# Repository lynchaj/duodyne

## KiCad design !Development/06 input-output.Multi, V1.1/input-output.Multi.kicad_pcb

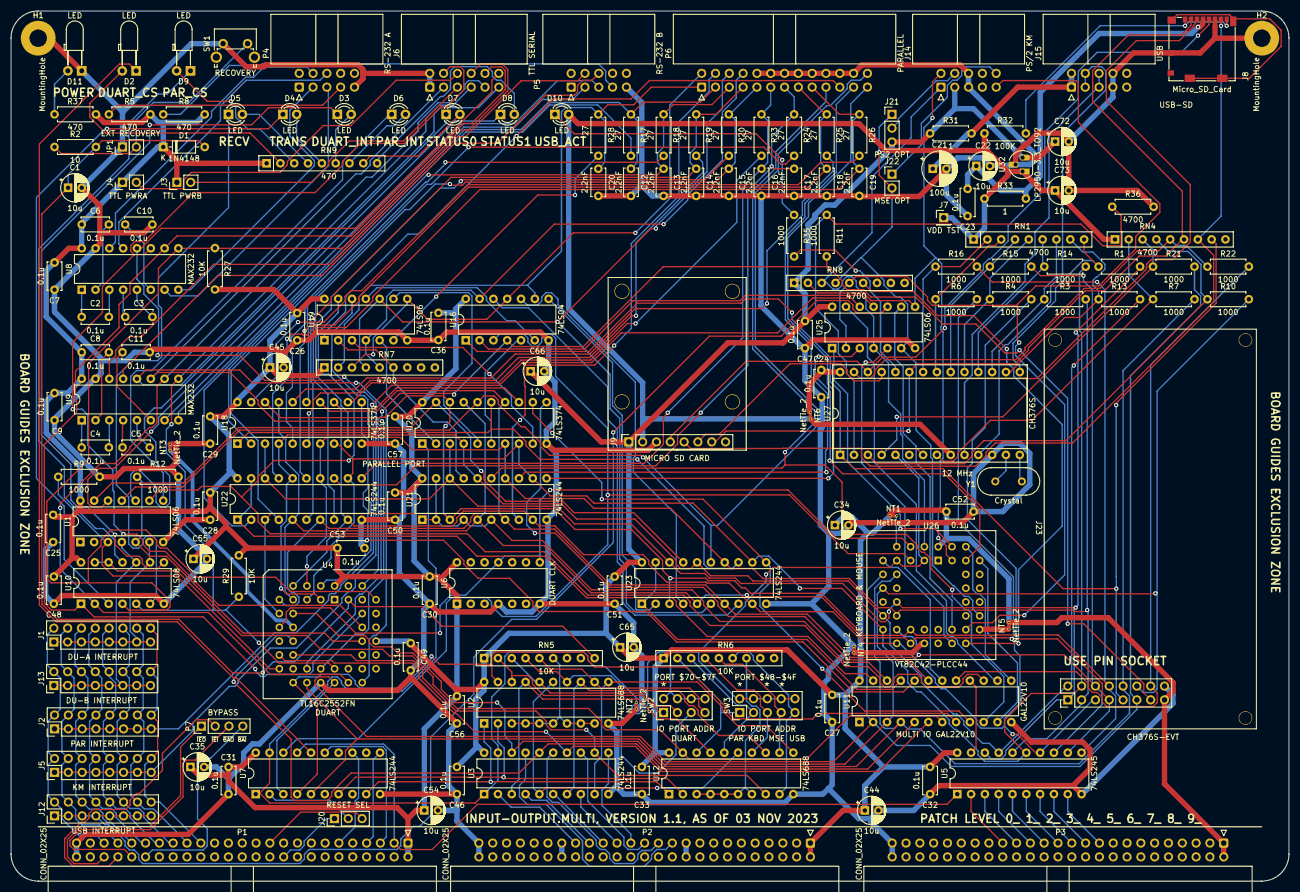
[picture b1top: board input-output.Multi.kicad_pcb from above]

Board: 2 copper layers, 235.0 x 160.0 mm, 167 parts (0 on the bottom side), 230 nets.

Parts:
C1, C22, C34, C35, C44, C45, C54, C55, C65, C66, C72, C73: 10u; CP_Radial_D5.0mm_P2.50mm
C2, C3, C4, C5, C6, C7, C8, C9, C10, C11, C23, C24, C25, C26, C27, C28, C29, C30, C31, C32, C33, C36, C46, C47, C48, C49, C50, C51, C52, C53, C56, C57: 0.1u; C_Disc_D5.0mm_W2.5mm_P5.00mm
C12, C13, C14, C15, C16, C17, C18, C19, C20: 2.2nF; C_Disc_D5.0mm_W2.5mm_P5.00mm
C21: 100u; CP_Radial_D6.3mm_P2.50mm
D1: 1N4148; D_DO-35_SOD27_P7.62mm_Horizontal
D2, D9, D11: LED; LED_D3.0mm_Horizontal_O3.81mm_Z2.0mm
D3, D4, D5, D6, D7, D8, D10: LED; LED_D3.0mm
H1, H2: MountingHole; MountingHole_3.2mm_M3_Pad
J1: DU-A INTERRUPT; PinHeader_2x08_P2.54mm_Vertical
J2: PAR INTERRUPT; PinHeader_2x08_P2.54mm_Vertical
J3: TTL PWRB; PinHeader_1x02_P2.54mm_Vertical
J4: TTL PWRA; PinHeader_1x02_P2.54mm_Vertical
J5: KM INTERRUPT; PinHeader_2x08_P2.54mm_Vertical
J6: TTL SERIAL; IDC-Header_2x06_P2.54mm_Horizontal
J7: VDD TST; PinHeader_1x01_P2.54mm_Vertical
J8: Micro_SD_Card; microSD_HC_Molex_104031-0811
J9: MICRO SD CARD; Adafruit MicroSD Module
J12: USB INTERRUPT; PinHeader_2x08_P2.54mm_Vertical
J13: DU-B INTERRUPT; PinHeader_2x08_P2.54mm_Vertical
J14: PS/2 KM; IDC-Header_2x05_P2.54mm_Horizontal
J15: USB; IDC-Header_2x05_P2.54mm_Horizontal
J20: RESET SEL; PinHeader_1x03_P2.54mm_Vertical
J21: PS2 OPT; PinHeader_1x03_P2.54mm_Vertical
J22: MSE OPT; PinHeader_1x02_P2.54mm_Vertical
J23: CH376S-EVT
JP1: EXT RECOVERY; PinHeader_1x02_P2.54mm_Vertical
NT1, NT2, NT3, NT4, NT5, NT6: NetTie_2; NetTie-2_THT_Pad0.3mm
P1, P2, P3: CONN_02X25; IDC-Header_2x25_P2.54mm_Horizontal
P4: RS-232 A; IDC-Header_2x05_P2.54mm_Horizontal
P5: RS-232 B; IDC-Header_2x05_P2.54mm_Horizontal
P6: PARALLEL; IDC-Header_2x13_P2.54mm_Horizontal
P7: BYPASS; PinHeader_1x04_P2.54mm_Vertical
R1, R3, R4, R6, R7, R9, R10, R11, R12, R13, R14, R15, R16, R21, R22, R35: 1000; R_Axial_DIN0207_L6.3mm_D2.5mm_P7.62mm_Horizontal
R2: 10; R_Axial_DIN0207_L6.3mm_D2.5mm_P7.62mm_Horizontal
R5, R8, R37: 470; R_Axial_DIN0207_L6.3mm_D2.5mm_P7.62mm_Horizontal
R17, R18, R19, R20, R23, R24, R25, R26, R28: 27; R_Axial_DIN0207_L6.3mm_D2.5mm_P7.62mm_Horizontal
R27, R29: 10K; R_Axial_DIN0207_L6.3mm_D2.5mm_P7.62mm_Horizontal
R31, R33: 1; R_Axial_DIN0207_L6.3mm_D2.5mm_P7.62mm_Horizontal
R32: 100K; R_Axial_DIN0207_L6.3mm_D2.5mm_P7.62mm_Horizontal
R36: 4700; R_Axial_DIN0207_L6.3mm_D2.5mm_P7.62mm_Horizontal
RN1, RN4, RN7, RN8: 4700; R_Array_SIP9
RN5, RN6: 10K; R_Array_SIP9
RN9: 470; R_Array_SIP9
SW1: RECOVERY; SW_Tactile_SPST_Angled_PTS645Vx58-2LFS
SW2: IO PORT ADDR; PinHeader_2x04_P2.54mm_Vertical
SW3: IO PORT ADDR; PinHeader_2x05_P2.54mm_Vertical
U1, U19, U25: 74LS06; DIP-14_W7.62mm
U2, U12: 74LS688; DIP-20_W7.62mm
U3, U7, U21, U22, U23: 74LS244; DIP-20_W7.62mm
U4: TL16C2552FN; PLCC-44_THT-Socket
U5: 74LS245; DIP-20_W7.62mm
U6: DUART CLK; DIP-14_W7.62mm
U8, U9: MAX232; DIP-16_W7.62mm
U10: 74LS08; DIP-14_W7.62mm
U11: GAL22V10; DIP-24_W7.62mm
U16: 74LS04; DIP-14_W7.62mm
U18, U20: 74LS374; DIP-20_W7.62mm
U26: VT82C42-PLCC44; PLCC-44_THT-Socket
U27: CH376S; DIP-28_W15.24mm_Socket
U32: LP2950-3.3_TO92; TO-92_HandSolder
Y1: Crystal; Crystal_HC49-4H_Vertical

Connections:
470A: D2.2 (A), RN9.2 (R1)
470B: D9.2 (A), RN9.3 (R2)
470C: D5.2 (A), RN9.4 (R3)
470D: D4.2 (A), RN9.5 (R4)
470E: D3.2 (A), RN9.6 (R5)
470F: D6.2 (A), RN9.7 (R6)
470G: D7.2 (A), RN9.8 (R7)
470H: D8.2 (A), RN9.9 (R8)
+12V: P2.19, P2.20
-12V: P2.37, P2.38
/DUART/GND_UART: NT3.1, U4.12 (GND)
/DUART/INTA: R12.1, U1.5, U4.34 (INTA)
/DUART/INTB: R9.1, U1.3, U4.17 (INTB)
/DUART/RXA: P4.3, U8.8 (R2IN)
/DUART/RXB: P5.3, U9.8 (R2IN)
/DUART/TTL_RXA: J6.8, R27.1, U4.39 (RXA), U8.9 (R2OUT), U10.4
/DUART/TTL_RXB: J6.7, R29.1, U4.25 (RXB), U9.9 (R2OUT), U10.5
/DUART/TTL_TXA: J6.10, U4.38 (TXA), U8.10 (T2IN), U10.1
/DUART/TTL_TXB: J6.9, U4.26 (TXB), U9.10 (T2IN), U10.2
/DUART/TXA: P4.5, U8.7 (T2OUT)
/DUART/TXB: P5.5, U9.7 (T2OUT)
/DUART/~CTSA: P4.6, U8.13 (R1IN)
/DUART/~CTSB: P5.6, U9.13 (R1IN)
/DUART/~DTRA: P4.7, R5.1
/DUART/~DTRB: P5.7, R8.1
/DUART/~INTA: J1.1, J1.3, J1.5, J1.7, J1.9, J1.11, J1.13, J1.15, U1.6, U10.9
/DUART/~INTB: J13.1, J13.3, J13.5, J13.7, J13.9, J13.11, J13.13, J13.15, U1.4, U10.10
/DUART/~RTSA: P4.4, U8.14 (T1OUT)
/DUART/~RTSB: P5.4, U9.14 (T1OUT)
/DUART/~TTL_CTSA: J6.12, U4.40 (~CTSA), U8.12 (R1OUT)
/DUART/~TTL_CTSB: J6.11, U4.28 (~CTSB), U9.12 (R1OUT)
/DUART/~TTL_RIA: C1.1, D1.2 (A), R2.2, RN5.9 (R8), U4.43 (~RIA)
/DUART/~TTL_RTSA: J6.4, U4.36 (~RTSA), U8.11 (T1IN)
/DUART/~TTL_RTSB: J6.3, U4.23 (~RTSB), U9.11 (T1IN)
/USB-SD/RST: R11.1, R36.1, U27.2 (RSTI)
/USB-SD/SDCK: J8.5 (CLK), J9.4, U27.26 (SD_CK)
/USB-SD/SDCS: J8.2 (DAT3/CD), J9.7, RN4.6 (R5), U27.23 (SD_CS)
/USB-SD/SDDI: J8.3 (CMD), J9.6, U27.25 (SD_DO)
/USB-SD/SDDO: J8.7 (DAT0), J9.5, RN4.7 (R6), U27.7 (SD_DI)
/USB-SD/UD+: J15.5, J15.6, U27.10 (UD+)
/USB-SD/UD-: J15.3, J15.4, U27.11 (UD-)
/USB-SD/VBUS: C21.1, J15.1, J15.2, R31.2
/USB-SD/VDD2: C24.1, NT6.1, U27.28 (VCC)
/USB-SD/VDD3: C22.1, C23.1, J8.4 (VDD), R33.2
/USB-SD/~INT-USB: J23.9, RN4.8 (R7), U16.1, U27.1 (~INT)
/kbdmse/KBDCLK: J14.1, RN8.3 (R2), U25.4, U26.2 (T0)
/kbdmse/KBDDAT: J14.9, RN8.5 (R4), U25.2, U26.30 (P10)
/kbdmse/MSECLK: J14.2, RN8.2 (R1), U25.8, U26.43 (T1)
/kbdmse/MSEDAT: J21.1, J22.2, RN8.4 (R3), U25.6, U26.31 (P11)
/kbdmse/PROG: RN8.6 (R5), U26.28 (PROG)
/kbdmse/~INT_KM: J5.1, J5.3, J5.5, J5.7, J5.9, J5.11, J5.13, J5.15, U25.12
/parallel/BUSY: RN7.6 (R5), U19.2, U21.17 (I3b)
/parallel/ERROR: P6.4, U21.8 (I3a)
/parallel/P-RESET: P6.6, RN7.4 (R3), U19.10, U23.6 (I2a)
/parallel/PAPEROUT: P6.23, U21.13 (I1b)
/parallel/PD0: C12.1, P6.3, R17.1, U22.2 (I0a)
/parallel/PD1: C13.1, P6.5, R18.1, U22.4 (I1a)
/parallel/PD2: C14.1, P6.7, R19.1, U22.6 (I2a)
/parallel/PD3: C15.1, P6.9, R20.1, U22.8 (I3a)
/parallel/PD4: C16.1, P6.11, R23.1, U22.11 (I0b)
/parallel/PD5: C17.1, P6.13, R24.1, U22.13 (I1b)
/parallel/PD6: C18.1, P6.15, R25.1, U22.15 (I2b)
/parallel/PD7: C19.1, P6.17, R26.1, U22.17 (I3b)
/parallel/SELECT: P6.25, U21.11 (I0b)
/parallel/STATUS0: P6.26, U1.11, U20.16 (O6), U23.15 (I2b)
/parallel/STATUS1: U1.13, U20.19 (O7), U23.17 (I3b)
/parallel/~BUSY: P6.21, U19.1
/parallel/~INT_PAR: J2.1, J2.3, J2.5, J2.7, J2.9, J2.11, J2.13, J2.15, U19.12
/parallel/~LINEFEED: P6.2, RN7.3 (R2), U16.11, U19.8
/parallel/~PDENBL: U18.1 (OE), U20.15 (O5), U23.13 (I1b)
/parallel/~SEL: P6.8, RN7.5 (R4), U16.13, U19.4
/parallel/~STROBE: C20.1, P6.1, R28.1, RN7.2 (R1), U16.9
A0: P2.35, U3.2 (I0a)
A1: P2.33, U3.4 (I1a)
A2: P2.31, U3.6 (I2a)
A3: P2.29, U3.8 (I3a)
A4: P2.27, U3.11 (I0b)
A5: P2.25, U3.13 (I1b)
A6: P2.23, U3.15 (I2b)
A7: P2.21, U3.17 (I3b)
ACK: P6.19, U11.10 (I9), U21.15 (I2b)
CLK_DUART: U4.11 (XTAL1), U6.8, U6.11, U26.4 (X2)
D0: P3.33, U5.2 (A0)
D1: P3.31, U5.3 (A1)
D2: P3.29, U5.4 (A2)
D3: P3.27, U5.5 (A3)
D4: P3.25, U5.6 (A4)
D5: P3.23, U5.7 (A5)
D6: P3.21, U5.8 (A6)
D7: P3.19, U5.9 (A7)
GND: C1.2, C7.2, C9.2, C10.2, C11.2, C12.2, C13.2, C14.2, C15.2, C16.2, C17.2, C18.2, C19.2, C20.2, C21.2, C22.2, C23.2, C24.2, C25.2, C26.2, C27.2, C28.2, C29.2, C30.2, C31.2, C32.2, C33.2, C34.2, C35.2, C36.2, C44.2, C45.2, C46.2, C47.2, C48.2, C49.2, C50.2, C51.2, C52.2, C53.2, C54.2, C55.2, C56.2, C57.2, C65.2, C66.2, C72.2, C73.2, D11.1 (K), H1.1, H2.1, J6.1, J6.2, J8.6 (VSS), J8.9 (SHIELD), J9.3, J14.5, J14.6, J15.7, J15.8, J23.16, JP1.1 (A), NT2.1, NT3.2, NT4.1, P1.49, P1.50, P2.49, P2.50, P3.49, P3.50, P4.9, P5.9, P6.10, P6.12, P6.14, P6.16, P6.18, P6.20, P6.22, P6.24, R9.2, R12.2, R36.2, SW1.1, U1.7 (GND), U2.10 (GND), U3.10 (GND), U4.22 (GND), U5.10 (GND), U6.4, U6.7, U7.10 (GND), U8.15 (GND), U9.15 (GND), U10.7 (GND), U11.12 (GND), U12.10 (GND), U16.7 (GND), U18.10 (GND), U19.7 (GND), U20.10 (GND), U21.10 (GND), U22.10 (GND), U23.10 (GND), U25.7 (GND), U27.12 (GND), U32.2 (GND)
INT_KM: U11.14 (O9), U25.13
INT_PAR: U1.9, U11.15 (O8), U19.13
unnamed: C2.1, U8.1 (C1+)
unnamed: C2.2, U8.3 (C1-)
unnamed: C3.1, U8.4 (C2+)
unnamed: C3.2, U8.5 (C2-)
unnamed: C4.1, U9.1 (C1+)
unnamed: C4.2, U9.3 (C1-)
unnamed: C5.1, U9.4 (C2+)
unnamed: C5.2, U9.5 (C2-)
unnamed: C6.2, U8.2 (VS+)
unnamed: C8.2, U9.2 (VS+)
unnamed: C10.1, U8.6 (VS-)
unnamed: C11.1, U9.6 (VS-)
unnamed: D2.1 (K), U7.16 (O1a)
unnamed: D3.1 (K), U10.8
unnamed: D4.1 (K), U10.3
unnamed: D5.1 (K), U10.6
unnamed: D6.1 (K), U1.8
unnamed: D7.1 (K), U1.10
unnamed: D8.1 (K), U1.12
unnamed: D9.1 (K), U10.11
unnamed: D10.1 (K), R35.1
unnamed: D11.2 (A), R37.1
unnamed: J3.2, J6.5
unnamed: J4.2, J6.6
unnamed: J8.1 (DAT2), J8.8 (DAT1), R32.2
unnamed: J12.1, J12.3, J12.5, J12.7, J12.9, J12.11, J12.13, J12.15, U25.10
unnamed: J14.4, J21.2
unnamed: J14.10, J22.1
unnamed: J20.2, U7.2 (I0a)
unnamed: JP1.2 (B), R2.1, SW1.2
unnamed: R1.1, RN1.9 (R8), U27.15 (D0)
unnamed: R3.1, RN1.7 (R6), U27.17 (D2)
unnamed: R4.1, RN1.5 (R4), U27.19 (D4)
unnamed: R6.1, RN1.3 (R2), U27.21 (D6)
unnamed: R7.1, RN4.2 (R1), U27.8 (A0)
unnamed: R10.1, RN4.4 (R3), U27.3 (~WR)
unnamed: R13.1, RN1.8 (R7), U27.16 (D1)
unnamed: R14.1, RN1.6 (R5), U27.18 (D3)
unnamed: R15.1, RN1.4 (R3), U27.20 (D5)
unnamed: R16.1, RN1.2 (R1), U27.22 (D7)
unnamed: R17.2, U18.2 (O0)
unnamed: R18.2, U18.5 (O1)
unnamed: R19.2, U18.6 (O2)
unnamed: R20.2, U18.9 (O3)
unnamed: R21.1, RN4.3 (R2), U27.4 (~RD)
unnamed: R22.1, RN4.5 (R4), U27.27 (~PCS)
unnamed: R23.2, U18.12 (O4)
unnamed: R24.2, U18.15 (O5)
unnamed: R25.2, U18.16 (O6)
unnamed: R26.2, U18.19 (O7)
unnamed: R28.2, U19.6
unnamed: R35.2, U27.24 (~ACT)
unnamed: RN5.2 (R1), SW2.1, U2.18 (R7)
unnamed: RN5.3 (R2), SW2.3, U2.16 (R6)
unnamed: RN5.4 (R3), SW2.5, U2.14 (R5)
unnamed: RN5.5 (R4), SW2.7, U2.12 (R4)
unnamed: RN5.6 (R5), U2.3 (R0), U2.4 (P1), U2.5 (R1), U2.6 (P2), U2.7 (R2), U2.8 (P3), U2.9 (R3)
unnamed: RN6.2 (R1), SW3.1, U12.18 (R7)
unnamed: RN6.3 (R2), SW3.3, U12.16 (R6)
unnamed: RN6.4 (R3), SW3.5, U12.14 (R5)
unnamed: RN6.5 (R4), SW3.7, U12.12 (R4)
unnamed: RN6.6 (R5), SW3.9, U12.9 (R3)
unnamed: RN6.7 (R6), U12.3 (R0), U12.4 (P1), U12.5 (R1), U12.6 (P2), U12.7 (R2)
unnamed: U16.2, U25.11
unnamed: U16.5, U20.6 (O2)
unnamed: U16.6, U19.11
unnamed: U16.8, U23.2 (I0a)
unnamed: U16.10, U23.4 (I1a)
unnamed: U16.12, U23.8 (I3a)
unnamed: U19.3, U20.9 (O3)
unnamed: U19.5, U20.2 (O0)
unnamed: U19.9, U20.5 (O1)
unnamed: U25.1, U26.42 (P27/DAK)
unnamed: U25.3, U26.41 (P26/DRQ)
unnamed: U25.5, U26.26 (P22)
unnamed: U25.9, U26.27 (P23)
unnamed: U27.13 (XI), Y1.1
unnamed: U27.14 (XO), Y1.2
ONE: NT1.2, U26.6 (SS)
P24-OB: U11.11 (I10), U26.39 (P24/OB)
P25-BF: U11.13 (I11), U26.40 (P25/BF)
PARINT: U11.9 (I8), U20.12 (O4), U23.11 (I0b)
VCC: C6.1, C7.1, C8.1, C9.1, C25.1, C26.1, C27.1, C28.1, C29.1, C30.1, C31.1, C32.1, C33.1, C34.1, C35.1, C36.1, C44.1, C45.1, C46.1, C47.1, C48.1, C49.1, C50.1, C51.1, C52.1, C53.1, C54.1, C55.1, C56.1, C57.1, C65.1, C66.1, C72.1, D1.1 (K), J3.1, J4.1, J9.1, J14.3, J21.3, J23.15, NT1.1, NT5.2, P1.1, P1.2, P2.1, P2.2, P3.1, P3.2, R5.2, R8.2, R27.2, R29.2, R31.1, R37.2, RN5.1 (common), RN6.1 (common), RN7.1 (common), RN8.1 (common), RN9.1 (common), U1.14 (VCC), U2.20 (VCC), U3.20 (VCC), U4.33 (VCC), U4.44 (VCC), U5.20 (VCC), U6.1, U6.14, U7.20 (VCC), U8.16 (VCC), U9.16 (VCC), U10.14 (VCC), U11.24 (VCC), U12.20 (VCC), U16.14 (VCC), U18.20 (VCC), U19.14 (VCC), U20.20 (VCC), U21.20 (VCC), U22.20 (VCC), U23.20 (VCC), U25.14 (VCC), U26.44 (VCC), U32.3 (VI)
VDD: NT5.1, U26.29 (VDD)
VDD1: C73.1, D10.2 (A), J7.1, J9.2, NT6.2, R32.1, R33.1, RN1.1 (common), RN4.1 (common), U27.9 (V3), U32.1 (VO)
VSS: NT4.2, U26.22 (VSS)
ZERO: NT2.2, SW2.2, SW2.4, SW2.6, SW2.8, SW3.2, SW3.4, SW3.6, SW3.8, SW3.10, U3.1 (OEa), U3.19 (OEb), U7.1 (OEa), U7.19 (OEb), U20.1 (OE), U26.3 (X1), U26.8 (EA), U27.5 (TXD)
bA0: J23.10, R7.2, U3.18 (O0a), U4.10 (A0), U11.4 (I3), U26.10 (A0)
bA1: U3.16 (O1a), U4.14 (A1), U11.5 (I4)
bA2: U3.14 (O2a), U4.15 (A2), U11.6 (I5)
bA3: U3.12 (O3a), U4.16 (CHSEL), U12.8 (P3)
bA4: U2.11 (P4), U3.9 (O0b), U12.11 (P4)
bA5: U2.13 (P5), U3.7 (O1b), U12.13 (P5)
bA6: U2.15 (P6), U3.5 (O2b), U12.15 (P6)
bA7: U2.17 (P7), U3.3 (O3b), U12.17 (P7)
bD0: J23.1, R1.2, U4.2 (D0), U5.18 (B0), U18.3 (D0), U20.3 (D0), U21.18 (O0a), U22.18 (O0a), U23.18 (O0a), U26.14 (D0)
bD1: J23.2, R13.2, U4.3 (D1), U5.17 (B1), U18.4 (D1), U20.4 (D1), U21.16 (O1a), U22.16 (O1a), U23.16 (O1a), U26.15 (D1)
bD2: J23.3, R3.2, U4.4 (D2), U5.16 (B2), U18.7 (D2), U20.7 (D2), U21.14 (O2a), U22.14 (O2a), U23.14 (O2a), U26.16 (D2)
bD3: J23.4, R14.2, U4.5 (D3), U5.15 (B3), U18.8 (D3), U20.8 (D3), U21.12 (O3a), U22.12 (O3a), U23.12 (O3a), U26.17 (D3)
bD4: J23.5, R4.2, U4.6 (D4), U5.14 (B4), U18.13 (D4), U20.13 (D4), U21.9 (O0b), U22.9 (O0b), U23.9 (O0b), U26.18 (D4)
bD5: J23.6, R15.2, U4.7 (D5), U5.13 (B5), U18.14 (D5), U20.14 (D5), U21.7 (O1b), U22.7 (O1b), U23.7 (O1b), U26.19 (D5)
bD6: J23.7, R6.2, U4.8 (D6), U5.12 (B6), U18.17 (D6), U20.17 (D6), U21.5 (O2b), U22.5 (O2b), U23.5 (O2b), U26.20 (D6)
bD7: J23.8, R16.2, U4.9 (D7), U5.11 (B7), U18.18 (D7), U20.18 (D7), U21.3 (O3b), U22.3 (O3b), U23.3 (O3b), U26.21 (D7)
bRESET: J23.13, R11.2, U4.21 (RESET), U16.4
~BAI: P1.40, P7.4
~BAO: P1.42, P7.3
~BUS_EN: U5.19 (CE), U11.16 (O7)
~CS_DUART: U2.19 (P=R), U4.18 (~CS), U7.4 (I1a), U11.8 (I7)
~CS_KM: U11.18 (O5), U26.7 (CS)
~CS_PAR: U10.12, U10.13, U11.7 (I6), U12.19 (P=R)
~CS_US: J23.14, R22.2, U11.17 (O6)
~EIRQ0: J1.2, J2.2, J5.2, J12.2, J13.2, P1.45
~EIRQ1: J1.4, J2.4, J5.4, J12.4, J13.4, P1.43
~EIRQ2: J1.6, J2.6, J5.6, J12.6, J13.6, P1.41
~EIRQ3: J1.8, J2.8, J5.8, J12.8, J13.8, P1.39
~EIRQ4: J1.10, J2.10, J5.10, J12.10, J13.10, P1.37
~EIRQ5: J1.12, J2.12, J5.12, J12.12, J13.12, P1.35
~EIRQ6: J1.14, J2.14, J5.14, J12.14, J13.14, P1.33
~EIRQ7: J1.16, J2.16, J5.16, J12.16, J13.16, P1.31
~IEI: P1.44, P7.2
~IEO: P1.46, P7.1
~IORQ: P1.7, U7.11 (I0b)
~M1: P1.11, U7.13 (I1b)
~PARIN0: U11.23 (O0), U22.1 (OEa), U22.19 (OEb)
~PARIN1: U11.22 (O1), U21.1 (OEa), U21.2 (I0a), U21.4 (I1a), U21.6 (I2a), U21.19 (OEb)
~PARIN2: U11.21 (O2), U23.1 (OEa), U23.19 (OEb)
~PAROUT0: U11.20 (O3), U18.11 (Cp)
~PAROUT2: U11.19 (O4), U20.11 (Cp)
~RD: P1.3, U5.1 (A->B), U7.17 (I3b)
~RES_IN: J20.1, P1.20
~RES_OUT: J20.3, P1.21
~WR: P1.5, U7.15 (I2b)
~bIORQ: U2.1 (G), U7.9 (O0b), U12.1 (G)
~bM1: U2.2 (P0), U7.7 (O1b), U12.2 (P0)
~bRD: J23.11, R21.2, U4.24 (~IOR), U7.3 (O3b), U11.2 (I1), U26.9 (RD)
~bRESET: U7.18 (O0a), U16.3, U26.5 (RESET)
~bWR: J23.12, R10.2, U4.20 (~IOW), U7.5 (O2b), U11.3 (I2), U26.11 (WR)

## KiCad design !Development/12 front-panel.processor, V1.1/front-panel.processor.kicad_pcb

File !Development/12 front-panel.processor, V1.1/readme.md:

The front-panel board connects to the Z80 processor to allow local access to configuration status input and display.  Also supports TTL serial to USB connection, an SSD1306 OLED display, and an I2C to SD card.  Several Z80 processor parameters can be set along with a reset button.

The I2C to SD card uses an ATtiny microcontroller which requires programming to work.  It is modeled after the I2C to SD card project at Technoblogy (http://www.technoblogy.com/show?3XEP)

Firmware for the card can be built and programed from the Arduino project located in the ATTINY_SD_FIRMWARE folder in this repo

You can program your ATtiny using the Arduino IDE for Linux 1.8.13 available here: https://www.arduino.cc/en/software/OldSoftwareReleases

with the megaTinyCore available here: https://wolles-elektronikkiste.de/en/using-megatinycore#usb2ttl_adaper_as_updi

I used a 3.3V TTL serial to USB cable direct to the UPDI connector on the front-panel and it worked fine. Following the instructions, I was able to successfully program the ATtiny1614 in-circuit. Alternatively, you can use pymcuprog on Linux.  Just follow the instructions here:https://pypi.org/project/pymcuprog/

For example, I was able to "ping" the ATtiny1614 and get a verbose status using: pymcuprog ping -d attiny1614 -t uart -u /dev/ttyUSB0 -v debug

Once programmed the ATTINY will respond to the I2C address 0x25.   This address can be updated in the code by changing the line 
```
const int MyAddress = 0x25;
```

The communication flow to the SD-I2C controller is very simple.  There are only 4 commands (I)nfo, (S)et block, (R)ead, (W)rite.  The SD-I2C controller expects a FAT formatted SD card with an raw HDD image file in the root directory called "IMAGE.IMG".   Cubix, DOS/65, or RomWBW image files should work without modification.

```
Info Command:
   Send one I2C data frame containing a single byte:  'I'   (This tells the controller to put the SD information in the buffer)
   Send one I2C data frame containing a single byte:  'R'   (This tells the controller that the host system wants to read the buffer)
   Read one I2C data frame -- should return 6 bytes:  'S' 'D' Byte1 Byte2 Byte3 Byte4  (the 4 bytes is one Double word containing the length in bytes of the image file- Big Endian)
   
Set Block Command:
   Send one I2C data frame containing 5 bytes:  'S' Byte1 Byte2 Byte3 Byte4  (the 4 bytes is one Double word containing the LBA block number that you wish to access in the image file- Big Endian)  
   
Read Command:
   Send one I2C data frame containing a single byte:  'R'   (This tells the controller that the host system wants to read the buffer)
   Read one I2C data frame -- should return 512 bytes 

Write Command:
   Send one I2C data frame containing  513 bytes:  'W' (512 bytes of sector data)  
```

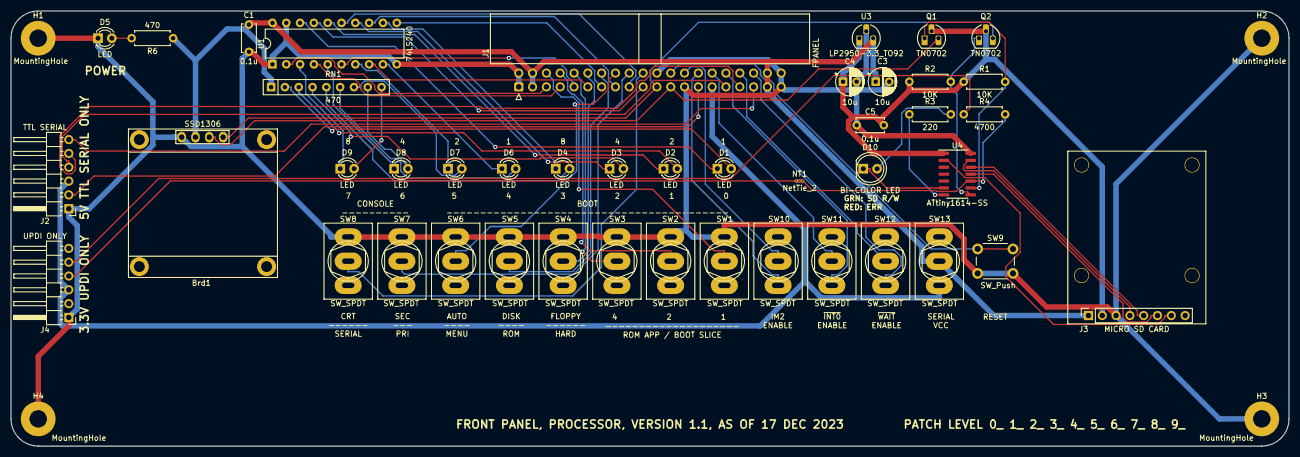
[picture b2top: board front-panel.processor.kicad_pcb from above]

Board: 2 copper layers, 235.0 x 80.0 mm, 48 parts (0 on the bottom side), 62 nets.

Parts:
Brd1: SSD1306; 128x64OLED
C1, C5: 0.1u; C_Disc_D5.0mm_W2.5mm_P5.00mm
C3, C4: 10u; CP_Radial_D5.0mm_P2.50mm
D1, D2, D3, D4, D5, D6, D7, D8, D9: LED; LED_D3.0mm
D10: BI-COLOR LED; LED_D5.0mm
H1, H2, H3, H4: MountingHole; MountingHole_3.2mm_M3_Pad
J1: FPANEL; IDC-Header_2x20_P2.54mm_Horizontal
J2: TTL SERIAL; PinHeader_1x06_P2.54mm_Horizontal
J3: MICRO SD CARD; Adafruit MicroSD Module
J4: UPDI ONLY; PinHeader_1x06_P2.54mm_Horizontal
NT1: NetTie_2; NetTie-2_THT_Pad0.3mm
Q1, Q2: TN0702; TO-92_HandSolder
R1, R2: 10K; R_Axial_DIN0207_L6.3mm_D2.5mm_P7.62mm_Horizontal
R3: 220; R_Axial_DIN0207_L6.3mm_D2.5mm_P7.62mm_Horizontal
R4: 4700; R_Axial_DIN0207_L6.3mm_D2.5mm_P7.62mm_Horizontal
R6: 470; R_Axial_DIN0207_L6.3mm_D2.5mm_P7.62mm_Horizontal
RN1: 470; R_Array_SIP9
SW1, SW2, SW3, SW4, SW5, SW6, SW7, SW8, SW10, SW11, SW12, SW13: SW_SPDT; SW_Toggle_Blue_wSlots
SW9: SW_Push; SW_PUSH_6mm
U1: 74LS240; DIP-20_W7.62mm
U3: LP2950-3.3_TO92; TO-92_HandSolder
U4: ATtiny1614-SS; SOIC-14_3.9x8.7mm_P1.27mm

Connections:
/CLK: J3.4, U4.13 (PA3)
/CS: J3.7, U4.2 (PA4)
/DI: J3.6, U4.11 (PA1)
/DO: J3.5, U4.12 (PA2)
/FP-D0: J1.6, SW1.2 (B)
/FP-D1: J1.8, SW2.2 (B)
/FP-D2: J1.10, SW3.2 (B)
/FP-D3: J1.12, SW4.2 (B)
/FP-D4: J1.14, SW5.2 (B)
/FP-D5: J1.16, SW6.2 (B)
/FP-D6: J1.18, SW7.2 (B)
/FP-D7: J1.20, SW8.2 (B)
/LED0: J1.5, U1.2 (I0a)
/LED1: J1.7, U1.4 (I1a)
/LED2: J1.9, U1.6 (I2a)
/LED3: J1.11, U1.8 (I3a)
/LED4: J1.13, U1.11 (I0b)
/LED5: J1.15, U1.13 (I1b)
/LED6: J1.17, U1.15 (I2b)
/LED7: J1.19, U1.17 (I3b)
/UPDI: NT1.2, R4.2, U4.10 (~RESET/PA0)
/UPDI-RX: J4.4, NT1.1
/UPDI-TX: J4.5, R4.1
/VCC-TS: J1.29, J2.3, J4.3, SW13.3 (C)
GND: Brd1.1 (GND), C1.1, C3.2, C4.2, C5.1, D5.1 (K), H1.1, H2.1, H3.1, H4.1, J1.1, J1.2, J1.22, J1.25, J1.39, J1.40, J2.1, J3.3, J4.1, SW1.1 (A), SW2.1 (A), SW3.1 (A), SW4.1 (A), SW5.1 (A), SW6.1 (A), SW7.1 (A), SW8.1 (A), SW9.2, U1.1 (OEa), U1.10 (GND), U1.19 (OEb), U3.2 (GND), U4.14 (GND)
I2C_SCL: Brd1.3 (SCL), J1.23, Q1.3 (D)
I2C_SDA: Brd1.4 (SDA), J1.21, Q2.3 (D)
unnamed: D1.1 (K), U1.18 (O0a)
unnamed: D1.2 (A), RN1.2 (R1)
unnamed: D2.1 (K), U1.16 (O1a)
unnamed: D2.2 (A), RN1.3 (R2)
unnamed: D3.1 (K), U1.14 (O2a)
unnamed: D3.2 (A), RN1.4 (R3)
unnamed: D4.1 (K), U1.12 (O3a)
unnamed: D4.2 (A), RN1.5 (R4)
unnamed: D5.2 (A), R6.2
unnamed: D6.1 (K), U1.9 (O0b)
unnamed: D6.2 (A), RN1.6 (R5)
unnamed: D7.1 (K), U1.7 (O1b)
unnamed: D7.2 (A), RN1.7 (R6)
unnamed: D8.1 (K), U1.5 (O2b)
unnamed: D8.2 (A), RN1.8 (R7)
unnamed: D9.1 (K), U1.3 (O3b)
unnamed: D9.2 (A), RN1.9 (R8)
unnamed: D10.1 (KA), U4.6 (PB3)
unnamed: D10.2 (AK), R3.2
unnamed: Q1.1 (S), R1.2, U4.9 (PB0)
unnamed: Q2.1 (S), R2.2, U4.8 (PB1)
unnamed: R3.1, U4.7 (PB2)
RX: J1.31, J2.4
TX: J1.33, J2.5
VCC: Brd1.2 (VCC), C1.2, C3.1, J1.3, J1.4, J1.37, J1.38, J3.1, R6.1, RN1.1 (common), SW13.2 (B), U1.20 (VCC), U3.3 (VI)
VDD1: C4.1, C5.2, J3.2, Q1.2 (G), Q2.2 (G), R1.1, R2.1, U3.1 (VO), U4.1 (VCC)
~CTS: J1.35, J2.6
~EXT_RES: J1.24, SW9.1
~IM2-EN-OE: J1.28, SW10.3 (C)
~IM2-EN: J1.26, SW10.2 (B)
~INT0-EN: J1.30, SW11.2 (B)
~INT0: J1.32, SW11.3 (C)
~RTS: J1.27, J2.2
~WAIT-EN: J1.34, SW12.2 (B)
~WAIT: J1.36, SW12.3 (C)
